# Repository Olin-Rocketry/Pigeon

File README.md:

# Pigeon
simple flight computer to serve as a learning bed for embedded software and pcb design.

## Features
- atmega328p-AU
- battery connector (JST-PH 2-pin)
- 3-axis accelerometer (ADXL345)
- 2 or 3 programming leds
- SD-Card reader
-level stepper for SD-Card

## Requirements
- fit in our current rocket (same dimensions as peregrine)
- run time greater than 30 minutes

## Goals
- learning platform for incoming members
- test/optimize SD-Card write performance

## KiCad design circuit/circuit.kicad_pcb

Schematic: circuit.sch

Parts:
C1, C8: C_1uF; C_0805_OEM; MPN 1276-2887-1-ND
C2, C3: C_10uF; C_0805_OEM; MPN 1276-1052-1-ND
C4, C5: C_30pF; C_0805_OEM; MPN 1276-1130-1-ND
C6: C_100pF; C_0805_OEM; MPN 732-7852-1-ND
C7, C9: C_0.1uF; C_0805_OEM; MPN 478-3352-1-ND
D1, D2, D3: LED_0805; LED_0805_OEM; MPN 475-1410-1-ND
J1: JST-PH_2_RA
J2: CONN_02X03; Pin_Header_Straight_2x03; MPN 609-3234-ND
R1, R2, R3, R5: R_200; R_0805_OEM; MPN RMCF0805JT200RCT-ND
R4, R6, R8, R9, R11: R_10K; R_0805_OEM; MPN CRS0805-FX-1002ELFCT-ND
R7: R_100; R_0805_OEM; MPN RNCP0805FTD100RCT-ND
SD1: MicroSD_V2; Micro_SD_Card_Holder_Molex; MPN 0473521001; Digi-Key Part Number WM3290CT-ND
U1: SK812; SK6812
U2: LM1117MPX-3.3; SOT-223
U3: ADXL345; MPN ADXL345BCCZ-ND
U4: ATmega328-AU; TQFP-32_7x7mm_Pitch0.8mm
Y1: Crystal_SMD; Crystal_SMD_FA238; MPN SER3686CT-ND

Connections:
/Battery+: C2.1, J1.1, U2.3
/Dectect_LED: R2.1, SD1.9, U4.12 (PB0)
/INT1: U3.8, U4.14 (PB2)
/INT2: U3.9, U4.13 (PB1)
/MISO: J2.1, SD1.7, U4.16 (PB4)
/MOSI: J2.4, SD1.3, U4.15 (PB3)
/Neopix: R5.2, U4.26 (PC3)
/P_LED_1: D2.2, U4.24 (PC1)
/RESET: J2.5, R6.1, U4.29 (~RESET~/PC6)
/SCK: J2.3, SD1.5, U4.17 (PB5)
/SCL: R4.2, U3.14, U4.28 (PC5)
/SDA: R8.2, U3.13, U4.27 (PC4)
/SD_CS: SD1.2, U4.11 (PD7)
GND: C1.2, C2.2, C3.2, C4.2, C5.2, C6.2, C7.1, C8.2, C9.2, D1.1, J1.2, J2.6, R1.1, R3.1, R11.2, SD1.6, U1.1, U2.1, U3.2, U3.4, U3.5, U4.3 (GND), U4.5 (GND), U4.21 (GND), Y1.2, Y1.4
unnamed: C4.1, U4.7 (XTAL1/PB6), Y1.1
unnamed: C5.1, U4.8 (XTAL2/PB7), Y1.3
unnamed: C6.1, R7.2, U4.18 (AVCC)
unnamed: D1.2, R2.2
unnamed: D2.1, R1.2
unnamed: D3.1, R3.2
unnamed: R5.1, U1.2
unnamed: R9.2, U3.7
unnamed: R11.1, U3.12
VCC: C1.1, C3.1, C7.2, C8.1, C9.1, D3.2, J2.2, R4.1, R6.2, R7.1, R8.1, R9.1, SD1.4, U1.3, U2.2, U2.4, U3.1, U3.6, U4.4 (VCC), U4.6 (VCC)

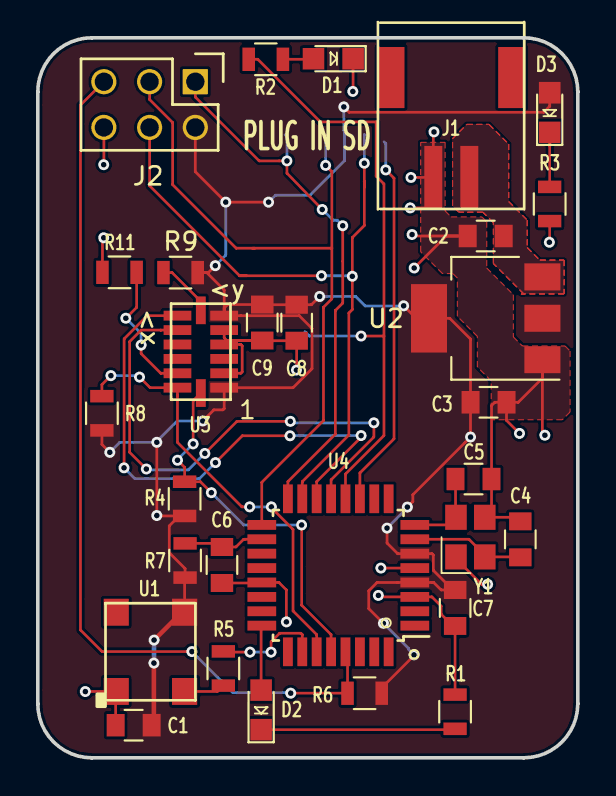
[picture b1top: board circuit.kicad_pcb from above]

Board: 2 copper layers, 30.0 x 40.0 mm, 30 parts (1 on the bottom side), 24 nets.

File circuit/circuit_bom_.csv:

Component,Description,Part,References,Value,Footprint,Quantity Per PCB,Datasheet,MFN,MPN,PurchasingLink,Purchasing Link,Digi-Key Part Number
1,b'',b'C_0.1uF',b'C2',b'C_0.1uF',b'C_0805_OEM',b'1',b'http://datasheets.avx.com/X7RDielectric.pdf',b'DK',b'478-3352-1-ND',b'https://www.digikey.com/products/en?keywords=478-3352-1-ND',b'',b''
2,b'',b'C_0.1uF',b'C7',b'C_0.1uF',b'C_0805_OEM',b'1',b'http://datasheets.avx.com/X7RDielectric.pdf',b'DK',b'478-3352-1-ND',b'https://www.digikey.com/products/en?keywords=478-3352-1-ND',b'',b''
3,b'',b'C_0.1uF',b'C9',b'C_0.1uF',b'C_0805_OEM',b'1',b'http://datasheets.avx.com/X7RDielectric.pdf',b'DK',b'478-3352-1-ND',b'https://www.digikey.com/products/en?keywords=478-3352-1-ND',b'',b''
4,b'',b'C_100pF',b'C6',b'C_100pF',b'C_0805_OEM',b'1',b'https://katalog.we-online.de/pbs/datasheet/885012007057.pdf',b'DK',b'732-7852-1-ND',b'https://www.digikey.com/product-detail/en/wurth-electronics-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,b'',b''
5,b'',b'C_1uF',b'C1',b'C_1uF',b'C_0805_OEM',b'1',b'http://www.samsungsem.com/kr/support/product-search/mlcc/__i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,b'DK',b'1276-2887-1-ND',b'https://www.digikey.com/product-detail/en/samsung-electro-me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,b'',b''
6,b'',b'C_1uF',b'C3',b'C_1uF',b'C_0805_OEM',b'1',b'http://www.samsungsem.com/kr/support/product-search/mlcc/__i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,b'DK',b'1276-2887-1-ND',b'https://www.digikey.com/product-detail/en/samsung-electro-me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,b'',b''
7,b'',b'C_1uF',b'C8',b'C_1uF',b'C_0805_OEM',b'1',b'http://www.samsungsem.com/kr/support/product-search/mlcc/__i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,b'DK',b'1276-2887-1-ND',b'https://www.digikey.com/product-detail/en/samsung-electro-me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,b'',b''
8,b'',b'C_30pF',b'C4 C5',b'C_30pF',b'C_0805_OEM',b'2',b'https://media.digikey.com/pdf/Data%20Sheets/Samsung%20PDFs/C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,b'DK',b'1276-1130-1-ND',b'https://www.digikey.com/product-detail/en/samsung-electro-me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,b'',b''
9,b'',b'LED_0805',b'D1 D2 D3',b'LED_0805',b'LED_0805_OEM',b'3',b'http://www.osram-os.com/Graphics/XPic9/00078860_0.pdf',b'DK',b'475-1410-1-ND',b'https://www.digikey.com/products/en?keywords=475-1410-1-ND',b'',b''
10,b'',b'JST-PH_2_RA',b'J1',b'JST-PH_2_RA',b'JST-PH_2_RA',b'1',b'https://cdn-shop.adafruit.com/datasheets/17311.pdf',b'',b'',b'',b'https://www.adafruit.com/product/1769',b''
11,b'',b'R_100',b'R7',b'R_100',b'R_0805_OEM',b'1',b'https://www.seielect.com/Catalog/SEI-rncp.pdf',b'DK',b'RNCP0805FTD100RCT-ND',b'https://www.digikey.com/products/en?keywords=RNCP0805FTD100RCT-ND',b'',b''
12,b'',b'R_10K',b'R9 R11',b'R_10K',b'R_0805_OEM',b'2',b'http://www.bourns.com/data/global/pdfs/CRS.pdf',b'DK',b'CRS0805-FX-1002ELFCT-ND',b'https://www.digikey.com/products/en?keywords=CRS0805-FX-1002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,b'',b''
13,b'',b'R_10K',b'R4 R6',b'R_10K',b'R_0805_OEM',b'2',b'http://www.bourns.com/data/global/pdfs/CRS.pdf',b'DK',b'CRS0805-FX-1002ELFCT-ND',b'https://www.digikey.com/products/en?keywords=CRS0805-FX-1002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,b'',b''
14,b'',b'R_200',b'R1 R2 R3 R5',b'R_200',b'R_0805_OEM',b'4',b'https://www.seielect.com/Catalog/SEI-RMCF_RMCP.pdf',b'DK',b'RMCF0805JT200RCT-ND',b'https://www.digikey.com/products/en?keywords=RMCF0805JT200RCT-ND',b'',b''
15,b'',b'R_4.7K',b'R8 R10',b'R_4.7K',b'R_0805_OEM',b'2',b'http://www.yageo.com/documents/recent/PYu-RC_Group_51_RoHS_L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,b'DK',b'311-4.7KARCT-ND',b'https://www.digikey.com/product-detail/en/yageo/RC0805JR-074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,b'',b''
16,b'',b'Micro_SD_Card_A118117CT-ND',b'SD1',b'Micro_SD_Card_A118117CT-ND',b'Micro_SD_Card_A118117CT-ND',b'1',b'https://www.te.com/commerce/DocumentDelivery/DDEController?A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,b'',b'2201778-1',b'',b'',b'A118117CT-ND'
17,b'',b'4050_Logic_Buffer',b'U6',b'4050_Logic_Buffer',b'SOIC-16_3.9x9.9mm_Pitch1.27mm',b'1',b'www.ti.com/lit/ds/symlink/cd74hc4049.pdf',b'',b'',b'',b'https://www.digikey.com/product-detail/en/texas-instruments/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,b''
18,b'',b'ADXL345',b'U3',b'ADXL345',b'ADXL345',b'1',b'http://www.analog.com/media/en/technical-documentation/data-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,b'DK',b'ADXL345BCCZ-ND',b'https://www.digikey.com/product-detail/en/analog-devices-inc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,b'',b''
19,"b'20MHz, 32kB Flash, 2kB SRAM, 1kB EEPROM, TQFP-32'",b'ATmega328-AU',b'U4',b'ATmega328-AU',b'TQFP-32_7x7mm_Pitch0.8mm',b'1',b'http://ww1.microchip.com/downloads/en/DeviceDoc/ATmega328_P%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,b'',b'',b'',b'',b''
20,b'',b'SK812',b'U1',b'SK812',b'SK6812',b'1',b'https://cdn-shop.adafruit.com/product-files/1138/SK6812+LED+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,b'',b'',b'https://www.digikey.com/product-detail/en/adafruit-industrie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,b'',b''
21,b'',b'TCR2EF33LM',b'U2',b'TCR2EF33LM',b'SOT25',b'1',b'https://toshiba.semicon-storage.com/info/docget.jsp?did=1379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,b'',b'TCR2EF33LM(CTCT-ND',b'',b'https://www.digikey.com/product-detail/en/toshiba-semiconduc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,b''
22,b'',b'USB_MicroB',b'U5',b'USB_MicroB',b'USB_Micro-B_Molex-105017-0001',b'1',b'https://www.molex.com/pdm_docs/sd/1050170001_sd.pdf',b'DK',b'WM1399CT-ND',b'https://www.digikey.com/product-detail/en/molex-llc/10501700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,b'',b''
23,b'',b'Crystal_SMD',b'Y1',b'Crystal_SMD',b'Crystal_SMD_FA238',b'1',b'https://support.epson.biz/td/api/doc_check.php?dl=brief_FA-2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,b'DK',b'SER3686CT-ND',b'https://www.digikey.com/products/en?keywords=SER3686CT-ND',b'',b''





Component Groups:,23
Component Count:,32
Fitted Components:,32
Number of PCBs:,1
Total components:,32
Schematic Version:,
Schematic Date:,
BoM Date:,b'Tue 02 Apr 2019 08:23:06 PM EDT'
Schematic Source:,b'/home/william/Desktop/pigeon/circuit/circuit.sch'
KiCad Version:,b'Eeschema 5.0.0-fee4fd1~66~ubuntu16.04.1'

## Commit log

2019-01-30 added library
2019-01-30 First draft of the circuit schematic
2019-02-02 Pushing the changes to the schematic
2019-02-02 Pushing the new schematic
2019-02-06 added parts library
2019-02-06 updated schematic
2019-02-06 Alex's first part
2019-02-08 Version one of the schematic with footprints
2019-02-08 Pushing the footprint
2019-02-09 schematic edited
2019-02-13 Pushing the edited symbols and footprints
2019-02-13 We can final make the layout
2019-02-15 oh geez. windows and ubuntu
2019-02-17 modified schematic and layout:
2019-02-17 did some more work on the layout. added some graphics
2019-04-12 revision two
2019-04-12 starting rev 3
2019-04-12 Footprint for the Molex Micro sd card holder
2019-04-12 Molex Micro SD card holder corrected symbol
2019-04-15 updated new microsd footprint
2019-04-17 modified some stuff
2019-04-17 working on rev3
2019-04-17 Did some more vias and traces - I don't know if this board looks good
2019-04-17 Did some moving around of parts and made the layout cleaner. I think this looks better!
2019-04-21 pushing but not done
2019-04-24 Latest updates to the PCB design
2019-05-01 Final REV4 Board
2019-05-21 Layout with a 2x03 connector
2019-05-21 Schematic with a 2x03 connector
2019-05-22 Fixed the text labels and revision number.
2019-05-23 Added the pigeon mark on the back
2020-03-22 Created a folder to store the website for Olin Rocketry
2020-03-22 Pushing the website draft for Olin Rocketry
2020-04-17 Adding the newsletter and avionics subteam paragraphs
2020-07-03 2nd Draft
